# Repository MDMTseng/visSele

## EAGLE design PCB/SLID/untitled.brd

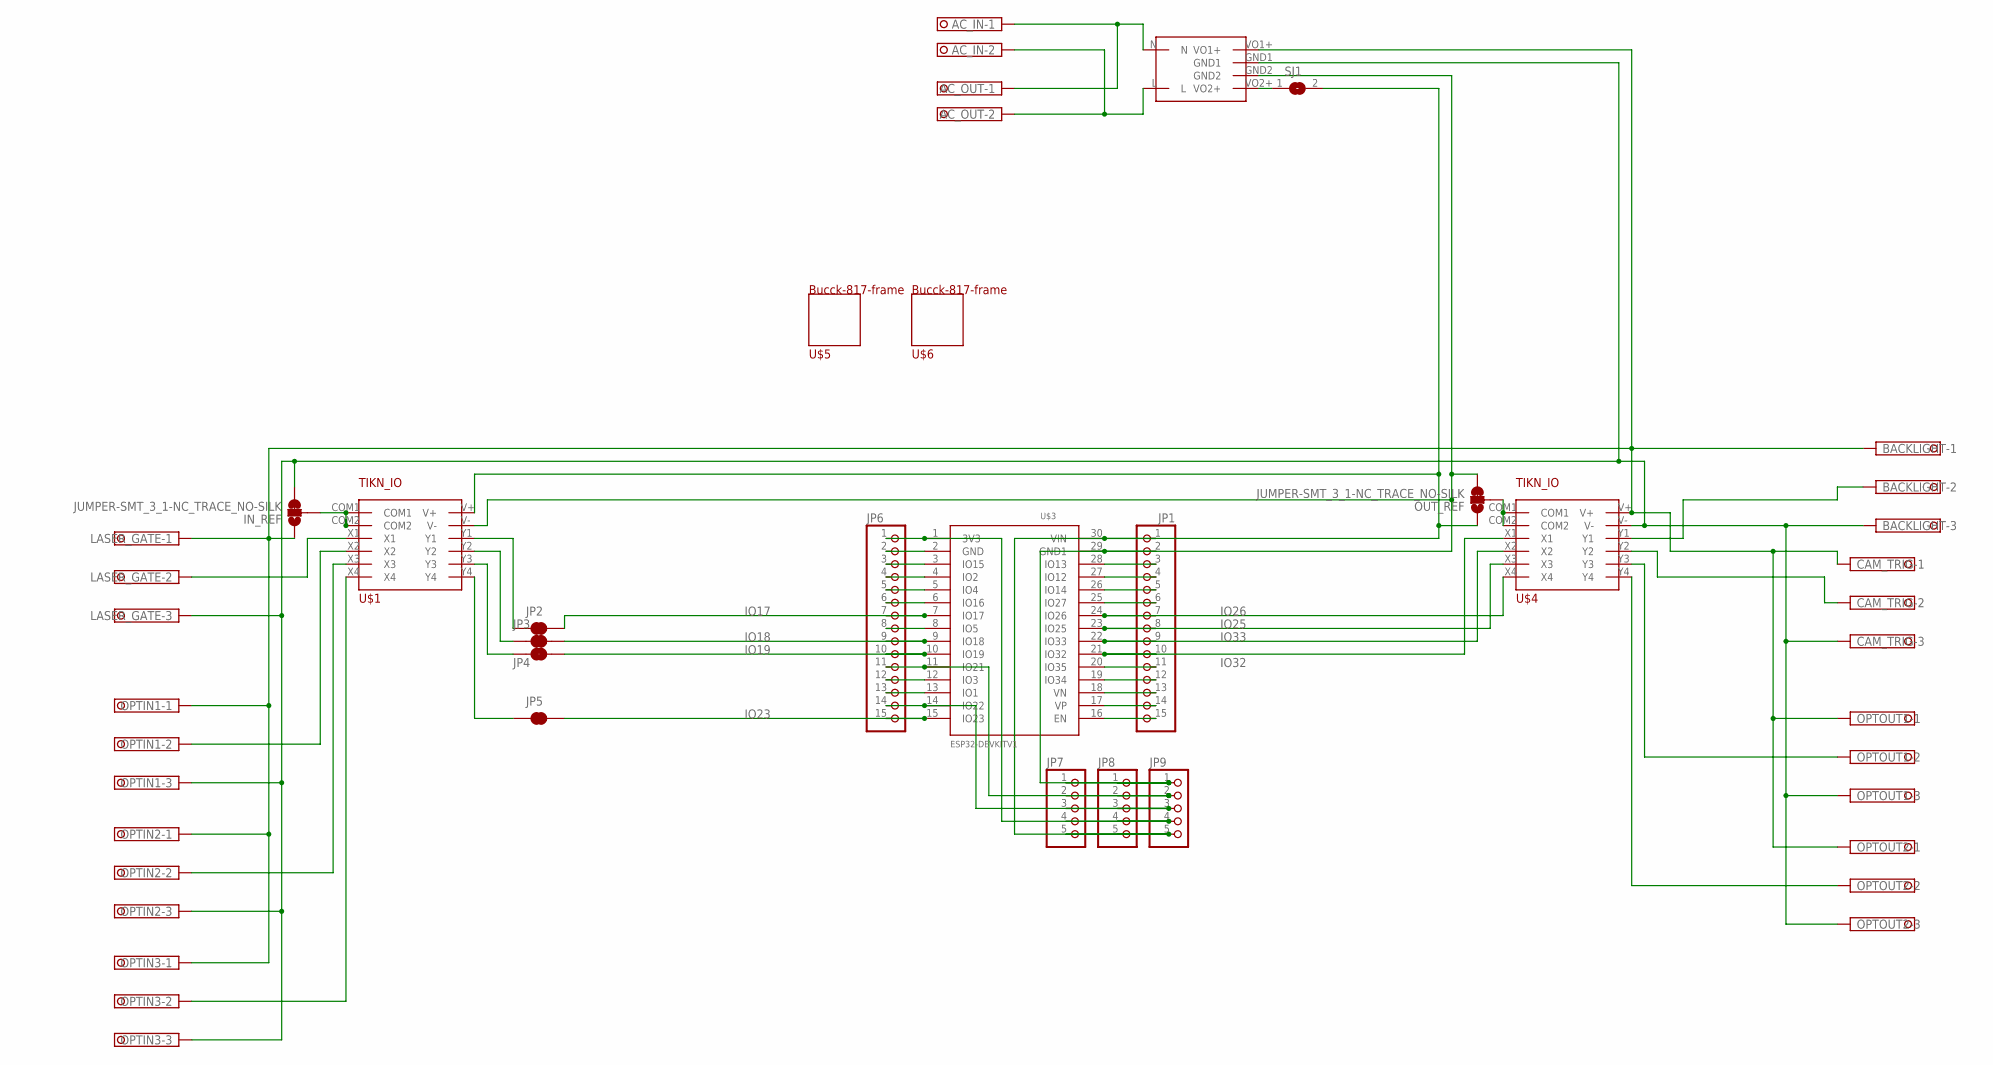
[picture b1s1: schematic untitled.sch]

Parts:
AC_IN: TERMINAL-BLOCK-3.5MM-2-PIN-LONG-PAD; TERMINAL-BLOCK-2-PIN-3.5MM-LONG-PAD
AC_OUT: TERMINAL-BLOCK-3.5MM-2-PIN-LONG-PAD; TERMINAL-BLOCK-2-PIN-3.5MM-LONG-PAD
BACKLIGHT: TERMINAL-BLOCK-3.5MM-3-PIN-LONG-PAD; TERMINAL-BLOCK-3-PIN-3.5MM-LONG-PAD
CAM_TRIG: TERMINAL-BLOCK-3.5MM-3-PIN-LONG-PAD; TERMINAL-BLOCK-3-PIN-3.5MM-LONG-PAD
IN_REF: JUMPER-SMT_3_1-NC_TRACE_NO-SILK; SMT-JUMPER_3_1-NC_TRACE_NO-SILK
JP1, JP6: PINHD-1X15; 1X15
JP2, JP3, JP4, JP5: JUMPER-SMT_2_NC_TRACE_SILK; SMT-JUMPER_2_NC_TRACE_SILK
JP7, JP8, JP9: PINHD-1X5; 1X05
LASER_GATE: TERMINAL-BLOCK-3.5MM-3-PIN-LONG-PAD; TERMINAL-BLOCK-3-PIN-3.5MM-LONG-PAD
OPTIN1, OPTIN2, OPTIN3: TERMINAL-BLOCK-3.5MM-3-PIN-LONG-PAD; TERMINAL-BLOCK-3-PIN-3.5MM-LONG-PAD
OPTOUT1, OPTOUT2: TERMINAL-BLOCK-3.5MM-3-PIN-LONG-PAD; TERMINAL-BLOCK-3-PIN-3.5MM-LONG-PAD
OUT_REF: JUMPER-SMT_3_1-NC_TRACE_NO-SILK; SMT-JUMPER_3_1-NC_TRACE_NO-SILK
SJ1: SJW
U$1, U$4: TIKN_IO_ISOLATOR2; IO_ISOLATOR2
U$2: AM22-24W1205V
U$3: ESP32DEVKITV1; ESP32-DEVKITV1
U$5, U$6: BUCC-817; BUCCK-817

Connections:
IO17: JP2.2, JP6.7, U$3.7 (IO17)
IO18: JP3.2, JP6.9, U$3.9 (IO18)
IO19: JP4.2, JP6.10, U$3.10 (IO19)
IO23: JP5.2, JP6.15, U$3.15 (IO23)
IO25: JP1.8, U$3.23 (IO25), U$4.X3
IO26: JP1.7, U$3.24 (IO26), U$4.X4
IO32: JP1.10, U$3.21 (IO32), U$4.X1
IO33: JP1.9, U$3.22 (IO33), U$4.X2
unnamed: JP1.1, JP7.5, JP8.5, JP9.5, OUT_REF.1, SJ1.2, U$1.V+, U$3.30 (VIN)
unnamed: SJ1.1, U$2.VO2+
unnamed: JP1.2, JP7.1, JP8.1, JP9.1, OUT_REF.3, U$1.V-, U$2.GND2, U$3.29 (GND1)
unnamed: BACKLIGHT.3, CAM_TRIG.3, IN_REF.3, LASER_GATE.3, OPTIN1.3, OPTIN2.3, OPTIN3.3, OPTOUT1.3, OPTOUT2.3, U$2.GND1, U$4.V-
unnamed: IN_REF.2, U$1.COM1, U$1.COM2
unnamed: OUT_REF.2, U$4.COM1, U$4.COM2
unnamed: JP2.1, U$1.Y1
unnamed: BACKLIGHT.1, CAM_TRIG.1, IN_REF.1, LASER_GATE.1, OPTIN1.1, OPTIN2.1, OPTIN3.1, OPTOUT1.1, OPTOUT2.1, U$2.VO1+, U$4.V+
unnamed: JP5.1, U$1.Y4
unnamed: JP4.1, U$1.Y3
unnamed: JP3.1, U$1.Y2
unnamed: JP6.8, U$3.8 (IO5)
unnamed: AC_IN.1, AC_OUT.1, U$2.N
unnamed: BACKLIGHT.2, U$4.Y1
unnamed: AC_IN.2, AC_OUT.2, U$2.L
unnamed: LASER_GATE.2, U$1.X1
unnamed: CAM_TRIG.2, U$4.Y2
unnamed: OPTIN1.2, U$1.X2
unnamed: OPTIN2.2, U$1.X3
unnamed: OPTIN3.2, U$1.X4
unnamed: OPTOUT1.2, U$4.Y3
unnamed: OPTOUT2.2, U$4.Y4
unnamed: JP6.1, JP7.4, JP8.4, JP9.4, U$3.1 (3V3)
unnamed: JP6.2, U$3.2 (GND)
unnamed: JP6.3, U$3.3 (IO15)
unnamed: JP6.4, U$3.4 (IO2)
unnamed: JP6.5, U$3.5 (IO4)
unnamed: JP6.6, U$3.6 (IO16)
unnamed: JP6.11, JP7.2, JP8.2, JP9.2, U$3.11 (IO21)
unnamed: JP6.12, U$3.12 (IO3)
unnamed: JP6.13, U$3.13 (IO1)
unnamed: JP6.14, JP7.3, JP8.3, JP9.3, U$3.14 (IO22)
unnamed: JP1.3, U$3.28 (IO13)
unnamed: JP1.4, U$3.27 (IO12)
unnamed: JP1.5, U$3.26 (IO14)
unnamed: JP1.6, U$3.25 (IO27)
unnamed: JP1.11, U$3.20 (IO35)
unnamed: JP1.12, U$3.19 (IO34)
unnamed: JP1.13, U$3.18 (VN)
unnamed: JP1.14, U$3.17 (VP)
unnamed: JP1.15, U$3.16 (EN)

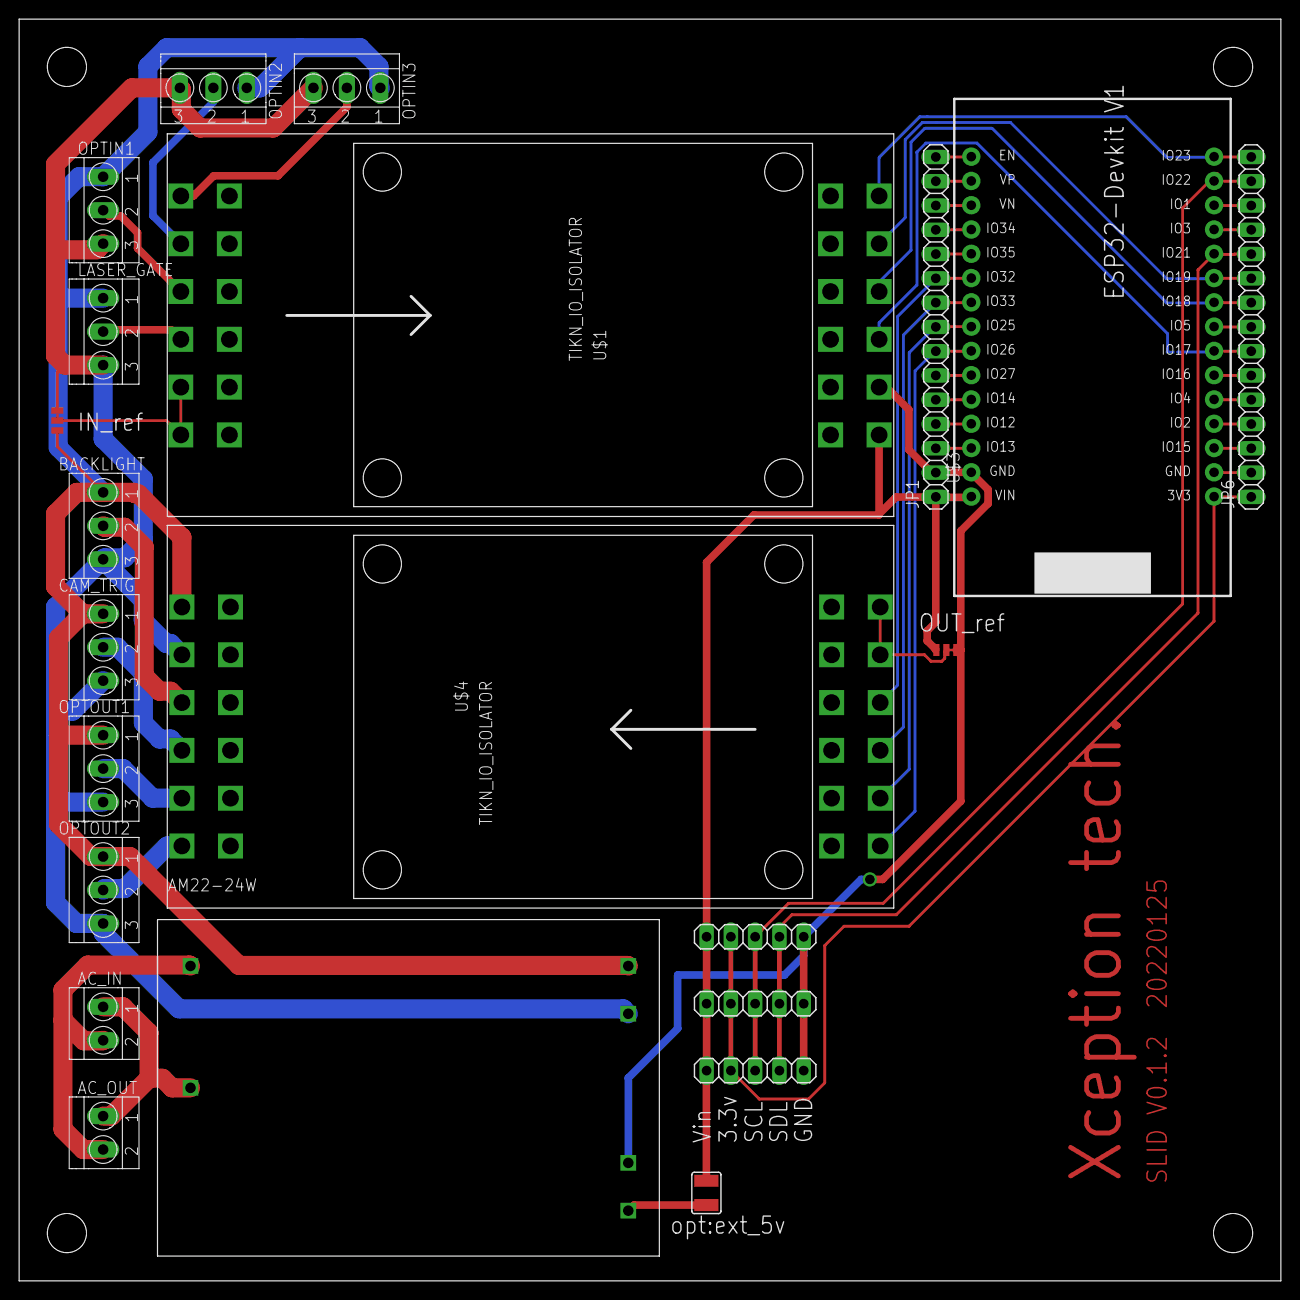
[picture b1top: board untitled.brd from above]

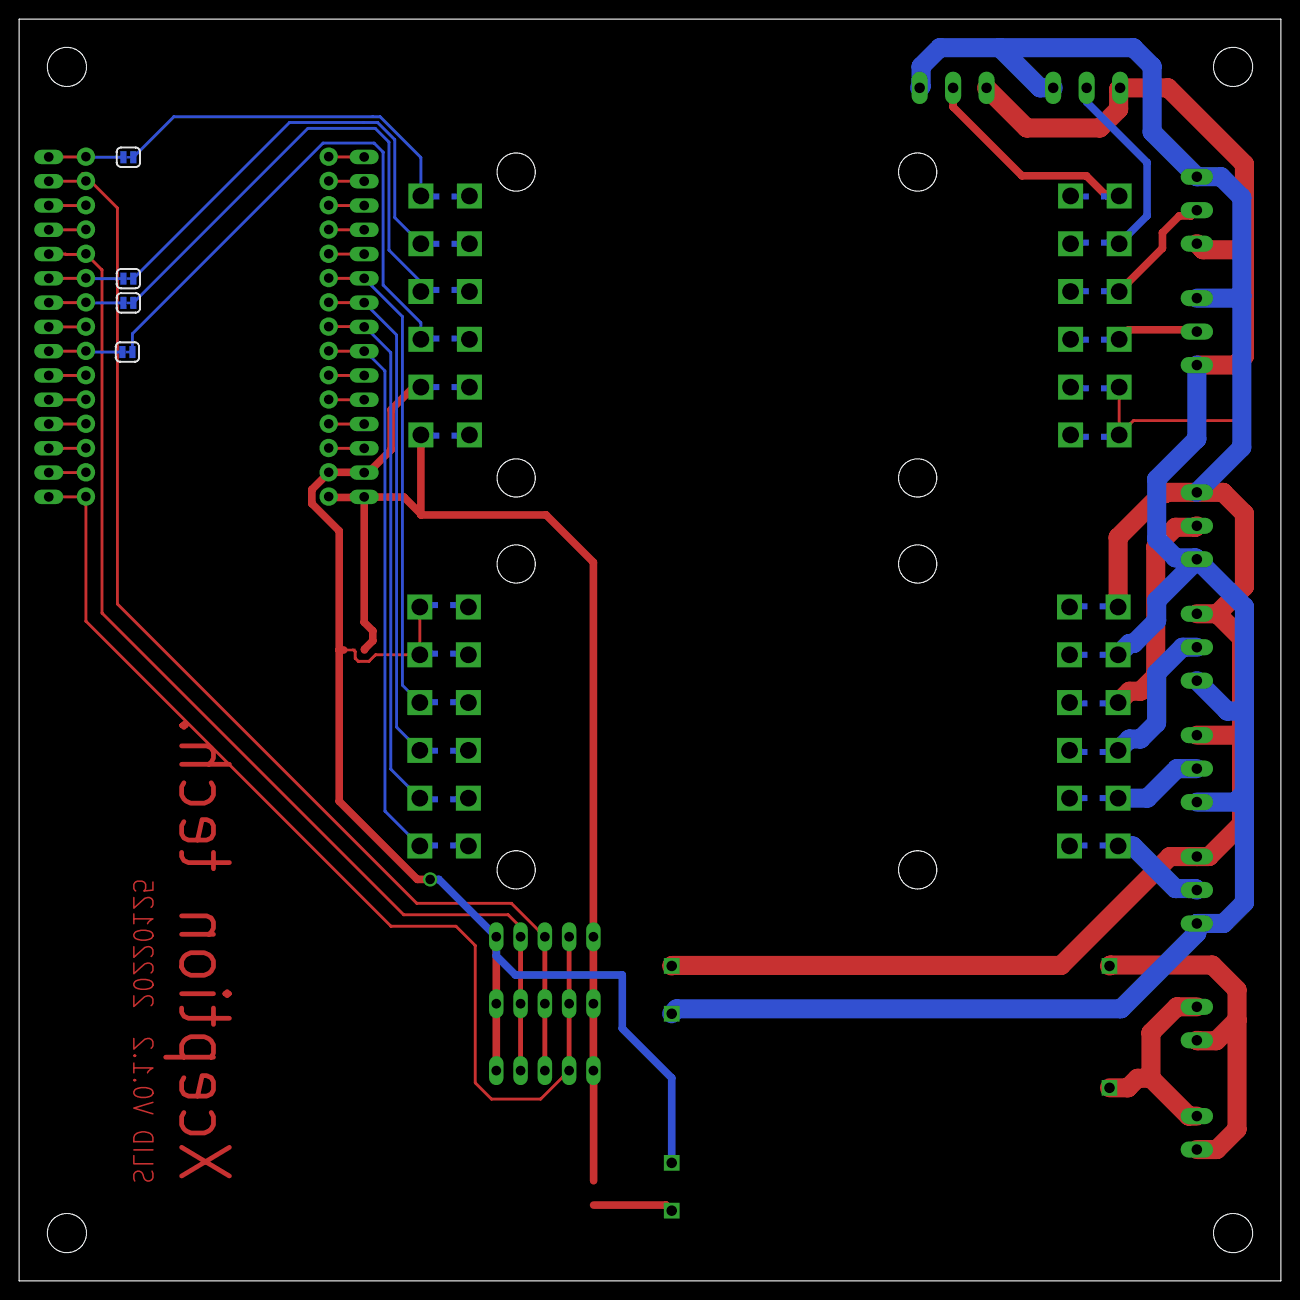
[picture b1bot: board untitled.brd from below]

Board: 2 copper layers, 132.0 x 132.0 mm, 28 parts (4 on the bottom side), 49 nets.

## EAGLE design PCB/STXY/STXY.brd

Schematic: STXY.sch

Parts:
C2: C2.5/2; C2.5-2
EIO1_A6, EIO1_A7, EIO1_A8: JUMPER-SMT_3_1-NC_TRACE_SILK; SMT-JUMPER_3_1-NC_TRACE_SILK
ETH0: WIZ820IO_DEVICE'DUAL-IN-LINE'; WIZ820IO
EXIO1, EXIO2: PCF8574T; SO16W
INT_JUMP1: JUMPER-SMT_3_1-NC_TRACE_SILK; SMT-JUMPER_3_1-NC_TRACE_SILK
J1, J2: F-1X20-SIP-100-32; SIP-100-20-32
J8, J10, J11, J12, J13, J14, J15, J17: F-2X12-DIL-100_M; DIL-100-2X12_M
JP1, JP2, JP3: JUMPER-SMT_3_1-NC_TRACE_SILK; SMT-JUMPER_3_1-NC_TRACE_SILK
J_SK9822: F-1X04-SIP-100-40Y; SIP-100-04-40Y
MOT1_!EN1, MOT1_!FLT1, MOT1_!RST1, MOT1_!SLP1, MOT1_M3, MOT1_M4, MOT1_M5, MOT1_MCU_GND1, MOT1_MCU_VDD1, MOT1_MD_DIR1, MOT1_MD_STEP1, MOT1_MOT_GND1, MOT1_MOT_VMOT1, MOT1_SENSOR_SFAR1, MOT1_SENSOR_SMID1, MOT1_SENSOR_SNEAR1, MOT1_SENSOR_VDD1, MOT2_!EN1, MOT2_!FLT1, MOT2_!RST1, MOT2_!SLP1, MOT2_M3, MOT2_M4, MOT2_M5, MOT2_MCU_GND1, MOT2_MCU_VDD1, MOT2_MD_DIR1, MOT2_MD_STEP1, MOT2_MOT_GND1, MOT2_MOT_VMOT1, MOT2_SENSOR_SFAR1, MOT2_SENSOR_SMID1, MOT2_SENSOR_SNEAR1, MOT2_SENSOR_VDD1, MOT3_!EN1, MOT3_!FLT1, MOT3_!RST1, MOT3_!SLP1, MOT3_M3, MOT3_M4, MOT3_M5, MOT3_MCU_GND1, MOT3_MCU_VDD1, MOT3_MD_DIR1, MOT3_MD_STEP1, MOT3_MOT_GND1, MOT3_MOT_VMOT1, MOT3_SENSOR_SFAR1, MOT3_SENSOR_SMID1, MOT3_SENSOR_SNEAR1, MOT3_SENSOR_VDD1: SHORTT5; SHORT_TOP-50
MOT1_CON1, MOT2_CON1, MOT3_CON1: F09VP
MOT1_DRV1, MOT2_DRV1, MOT3_DRV1: 2133-DRV8825; DRV8825
MOT1_DRV_OPT3, MOT2_DRV_OPT3, MOT3_DRV_OPT3: TERMINAL-BLOCK-3.5MM-9-PIN-ROUND-PAD; TERMINAL-BLOCK-9-PIN-3.5MM-ROUND-PAD
MOT1_DRV_OPT4, MOT2_DRV_OPT4, MOT3_DRV_OPT4: JST-XH-09-PIN-LONG-PAD; JST-XH-09-PACKAGE-LONG-PAD
POW_EUROSTYLE: TERMINAL-BLOCK-3.5MM-4-PIN-LONG-PAD; TERMINAL-BLOCK-4-PIN-3.5MM-LONG-PAD
R7, R8, R9, R10, R11, R12, R13, R14, R15, R16, R17, R18, R25, R26, R27, R28, R29, R30: 10KOHM-0603-1/10W-1%; 0603
U1: ESP32DEVKITC; ESP32-DEVKITC
X1: EMG_BTN; JST-XH-03-PACKAGE-LONG-PAD
X2: TERMINAL-BLOCK-3.5MM-3-PIN-LONG-PAD; TERMINAL-BLOCK-3-PIN-3.5MM-LONG-PAD
X3, X4, X5, X6, X7: JST-XH-12-PIN-LONG-PAD; JST-XH-12-PACKAGE-LONG-PAD

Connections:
EMG_SIG: J1.15, U1.15 (IO13), X1.3, X2.3
ETH0_INT: ETH0.J1.6 (/INT), EXIO2.12 (P7), X3.12, X4.12
EXIO1_INT: EXIO1.13 (!INT), J2.13, U1.31 (IO19)
EXT_5V: EXIO1.1 (A0), EXIO1.16 (VDD), EXIO2.2 (A1), EXIO2.16 (VDD), J1.19, JP1.3, JP2.1, JP3.3, J_SK9822.1, MOT1_MCU_VDD1.1, MOT1_SENSOR_VDD1.1, MOT2_MCU_VDD1.1, MOT2_SENSOR_VDD1.1, MOT3_MCU_VDD1.1, MOT3_SENSOR_VDD1.1, POW_EUROSTYLE.3, U1.19 (5V), X1.2, X2.2, X3.3, X4.3, X5.3, X6.3, X7.3; also elsewhere on the board
EXT_24V: MOT1_MOT_VMOT1.1, MOT2_MOT_VMOT1.1, MOT3_MOT_VMOT1.1, POW_EUROSTYLE.1, X3.1, X4.1, X5.1, X6.1, X7.1
EXT_24V_GND: MOT1_MOT_GND1.1, MOT2_MOT_GND1.1, MOT3_MOT_GND1.1, POW_EUROSTYLE.2, X3.2, X4.2, X5.2, X6.2, X7.2
EXT_GND: ETH0.J1.1 (GND1), ETH0.J1.2 (GND2), ETH0.J2.1 (GND3), EXIO1.2 (A1), EXIO1.3 (A2), EXIO1.8 (VSS), EXIO2.1 (A0), EXIO2.3 (A2), EXIO2.8 (VSS), INT_JUMP1.1, J1.14, J2.14, J2.20, JP1.1, JP2.3, JP3.1, J_SK9822.4, MOT1_!RST1.1, MOT1_!SLP1.1, MOT1_MCU_GND1.1, MOT2_!RST1.1, MOT2_!SLP1.1, MOT2_MCU_GND1.1, MOT3_!RST1.1, MOT3_!SLP1.1, MOT3_MCU_GND1.1, POW_EUROSTYLE.4, U1.14 (GND), U1.32 (GND), U1.38 (GND), X1.1, X2.1, X3.4, X4.4, X5.4, X6.4, X7.4; also elsewhere on the board
LED_ARR_CLK: J2.9, J_SK9822.2, U1.27 (IO16)
MOT1_!EN: MOT1_!EN1.2, MOT1_DRV1.1 (!EN), MOT1_DRV_OPT3.7, MOT1_DRV_OPT4.7
MOT1_!FLT: MOT1_!FLT1.2, MOT1_DRV1.10 (!FLT)
MOT1_!RST: MOT1_!RST1.2, MOT1_DRV1.5 (!RST)
MOT1_!SLP: MOT1_!SLP1.2, MOT1_DRV1.6 (!SLP)
MOT1_M0: MOT1_DRV1.2 (M0), MOT1_M3.2
MOT1_M1: MOT1_DRV1.3 (M1), MOT1_M4.2
MOT1_M2: MOT1_DRV1.4 (M2), MOT1_M5.2
MOT1_MCU_GND: MOT1_CON1.2, MOT1_DRV1.9 (GND1), MOT1_MCU_GND1.2, R8.1, R10.1, R12.1
MOT1_MCU_VDD: MOT1_MCU_VDD1.2, R7.2, R9.2, R11.2
MOT1_MD_DIR: MOT1_DRV1.8 (DIR), MOT1_DRV_OPT3.9, MOT1_DRV_OPT4.9, MOT1_MD_DIR1.2
MOT1_MD_STEP: MOT1_DRV1.7 (STEP), MOT1_DRV_OPT3.8, MOT1_DRV_OPT4.8, MOT1_MD_STEP1.2
MOT1_MOT_GND: MOT1_DRV1.15 (GND2), MOT1_DRV_OPT3.5, MOT1_DRV_OPT4.5, MOT1_MOT_GND1.2
MOT1_MOT_VMOT: MOT1_DRV1.16 (VMOT), MOT1_DRV_OPT3.6, MOT1_DRV_OPT4.6, MOT1_MOT_VMOT1.2
MOT1_SENSOR_SFAR: MOT1_CON1.5, MOT1_SENSOR_SFAR1.2, R11.1, R12.2
MOT1_SENSOR_SMID: MOT1_CON1.4, MOT1_SENSOR_SMID1.2, R9.1, R10.2
MOT1_SENSOR_SNEAR: MOT1_CON1.3, MOT1_SENSOR_SNEAR1.2, R7.1, R8.2
MOT1_SENSOR_VDD: MOT1_CON1.1, MOT1_SENSOR_VDD1.2
MOT1_SOCK_A+: MOT1_CON1.6, MOT1_DRV1.12 (A1), MOT1_DRV_OPT3.1, MOT1_DRV_OPT4.1
MOT1_SOCK_A-: MOT1_CON1.7, MOT1_DRV1.11 (A2), MOT1_DRV_OPT3.2, MOT1_DRV_OPT4.2
MOT1_SOCK_B+: MOT1_CON1.8, MOT1_DRV1.13 (B1), MOT1_DRV_OPT3.3, MOT1_DRV_OPT4.3
MOT1_SOCK_B-: MOT1_CON1.9, MOT1_DRV1.14 (B2), MOT1_DRV_OPT3.4, MOT1_DRV_OPT4.4
MOT2_!EN: MOT2_!EN1.2, MOT2_DRV1.1 (!EN), MOT2_DRV_OPT3.7, MOT2_DRV_OPT4.7
MOT2_!FLT: MOT2_!FLT1.2, MOT2_DRV1.10 (!FLT)
MOT2_!RST: MOT2_!RST1.2, MOT2_DRV1.5 (!RST)
MOT2_!SLP: MOT2_!SLP1.2, MOT2_DRV1.6 (!SLP)
MOT2_M0: MOT2_DRV1.2 (M0), MOT2_M3.2
MOT2_M1: MOT2_DRV1.3 (M1), MOT2_M4.2
MOT2_M2: MOT2_DRV1.4 (M2), MOT2_M5.2
MOT2_MCU_GND: MOT2_CON1.2, MOT2_DRV1.9 (GND1), MOT2_MCU_GND1.2, R14.1, R16.1, R18.1
MOT2_MCU_VDD: MOT2_MCU_VDD1.2, R13.2, R15.2, R17.2
MOT2_MD_DIR: MOT2_DRV1.8 (DIR), MOT2_DRV_OPT3.9, MOT2_DRV_OPT4.9, MOT2_MD_DIR1.2
MOT2_MD_STEP: MOT2_DRV1.7 (STEP), MOT2_DRV_OPT3.8, MOT2_DRV_OPT4.8, MOT2_MD_STEP1.2
MOT2_MOT_GND: MOT2_DRV1.15 (GND2), MOT2_DRV_OPT3.5, MOT2_DRV_OPT4.5, MOT2_MOT_GND1.2
MOT2_MOT_VMOT: MOT2_DRV1.16 (VMOT), MOT2_DRV_OPT3.6, MOT2_DRV_OPT4.6, MOT2_MOT_VMOT1.2
MOT2_SENSOR_SFAR: MOT2_CON1.5, MOT2_SENSOR_SFAR1.2, R17.1, R18.2
MOT2_SENSOR_SMID: MOT2_CON1.4, MOT2_SENSOR_SMID1.2, R15.1, R16.2
MOT2_SENSOR_SNEAR: MOT2_CON1.3, MOT2_SENSOR_SNEAR1.2, R13.1, R14.2
MOT2_SENSOR_VDD: MOT2_CON1.1, MOT2_SENSOR_VDD1.2
MOT2_SOCK_A+: MOT2_CON1.6, MOT2_DRV1.12 (A1), MOT2_DRV_OPT3.1, MOT2_DRV_OPT4.1
MOT2_SOCK_A-: MOT2_CON1.7, MOT2_DRV1.11 (A2), MOT2_DRV_OPT3.2, MOT2_DRV_OPT4.2
MOT2_SOCK_B+: MOT2_CON1.8, MOT2_DRV1.13 (B1), MOT2_DRV_OPT3.3, MOT2_DRV_OPT4.3
MOT2_SOCK_B-: MOT2_CON1.9, MOT2_DRV1.14 (B2), MOT2_DRV_OPT3.4, MOT2_DRV_OPT4.4
MOT3_!EN: MOT3_!EN1.2, MOT3_DRV1.1 (!EN), MOT3_DRV_OPT3.7, MOT3_DRV_OPT4.7
MOT3_!FLT: MOT3_!FLT1.2, MOT3_DRV1.10 (!FLT)
MOT3_!RST: MOT3_!RST1.2, MOT3_DRV1.5 (!RST)
MOT3_!SLP: MOT3_!SLP1.2, MOT3_DRV1.6 (!SLP)
MOT3_M0: MOT3_DRV1.2 (M0), MOT3_M3.2
MOT3_M1: MOT3_DRV1.3 (M1), MOT3_M4.2
MOT3_M2: MOT3_DRV1.4 (M2), MOT3_M5.2
MOT3_MCU_GND: MOT3_CON1.2, MOT3_DRV1.9 (GND1), MOT3_MCU_GND1.2, R26.1, R28.1, R30.1
MOT3_MCU_VDD: MOT3_MCU_VDD1.2, R25.2, R27.2, R29.2
MOT3_MD_DIR: MOT3_DRV1.8 (DIR), MOT3_DRV_OPT3.9, MOT3_DRV_OPT4.9, MOT3_MD_DIR1.2
MOT3_MD_STEP: MOT3_DRV1.7 (STEP), MOT3_DRV_OPT3.8, MOT3_DRV_OPT4.8, MOT3_MD_STEP1.2
MOT3_MOT_GND: MOT3_DRV1.15 (GND2), MOT3_DRV_OPT3.5, MOT3_DRV_OPT4.5, MOT3_MOT_GND1.2
MOT3_MOT_VMOT: MOT3_DRV1.16 (VMOT), MOT3_DRV_OPT3.6, MOT3_DRV_OPT4.6, MOT3_MOT_VMOT1.2
MOT3_SENSOR_SFAR: MOT3_CON1.5, MOT3_SENSOR_SFAR1.2, R29.1, R30.2
MOT3_SENSOR_SMID: MOT3_CON1.4, MOT3_SENSOR_SMID1.2, R27.1, R28.2
MOT3_SENSOR_SNEAR: MOT3_CON1.3, MOT3_SENSOR_SNEAR1.2, R25.1, R26.2
MOT3_SENSOR_VDD: MOT3_CON1.1, MOT3_SENSOR_VDD1.2
MOT3_SOCK_A+: MOT3_CON1.6, MOT3_DRV1.12 (A1), MOT3_DRV_OPT3.1, MOT3_DRV_OPT4.1
MOT3_SOCK_A-: MOT3_CON1.7, MOT3_DRV1.11 (A2), MOT3_DRV_OPT3.2, MOT3_DRV_OPT4.2
MOT3_SOCK_B+: MOT3_CON1.8, MOT3_DRV1.13 (B1), MOT3_DRV_OPT3.3, MOT3_DRV_OPT4.3
MOT3_SOCK_B-: MOT3_CON1.9, MOT3_DRV1.14 (B2), MOT3_DRV_OPT3.4, MOT3_DRV_OPT4.4
MOTXY_M0: JP1.2, MOT1_M3.1, MOT2_M3.1, MOT3_M3.1
MOTXY_M1: JP2.2, MOT1_M4.1, MOT2_M4.1, MOT3_M4.1
MOTXY_M2: JP3.2, MOT1_M5.1, MOT2_M5.1, MOT3_M5.1
MOTX_DIR: J1.12, MOT1_MD_DIR1.1, U1.12 (IO14)
MOTX_SENSOR_FAR: EXIO1.4 (P0), MOT1_SENSOR_SFAR1.1, X5.5, X6.5
MOTX_SENSOR_NEAR: EIO1_A6.2, MOT1_SENSOR_SNEAR1.1
MOTX_STEP: J1.11, MOT1_MD_STEP1.1, U1.11 (IO27)
MOTY_DIR: J1.10, MOT2_MD_DIR1.1, U1.10 (IO26)
MOTY_SENSOR_FAR: EXIO1.5 (P1), MOT2_SENSOR_SFAR1.1, X5.6, X6.6
MOTY_SENSOR_NEAR: EIO1_A7.2, MOT2_SENSOR_SNEAR1.1
MOTY_STEP: J1.9, MOT2_MD_STEP1.1, U1.9 (IO25)
MOTZ_DIR: J1.8, MOT3_MD_DIR1.1, U1.8 (IO33)
MOTZ_SENSOR_FAR: EXIO1.6 (P2), MOT3_SENSOR_SFAR1.1, X5.7, X6.7
MOTZ_SENSOR_NEAR: EIO1_A8.2, MOT3_SENSOR_SNEAR1.1
MOTZ_STEP: J1.7, MOT3_MD_STEP1.1, U1.7 (IO32)
MOT_EN: J1.13, MOT1_!EN1.1, MOT2_!EN1.1, MOT3_!EN1.1, U1.13 (IO12)
unnamed: EXIO1.12 (P7), X5.12, X6.12
unnamed: EXIO1.11 (P6), X5.11, X6.11
unnamed: EXIO2.4 (P0), X3.5, X4.5
unnamed: EXIO2.5 (P1), X3.6, X4.6
unnamed: EXIO2.6 (P2), X3.7, X4.7
unnamed: EXIO2.7 (P3), X3.8, X4.8
unnamed: EXIO2.9 (P4), X3.9, X4.9
unnamed: J1.18, U1.18 (CMD)
unnamed: EXIO2.10 (P5), X3.10, X4.10
unnamed: ETH0.J1.5 (/SS), INT_JUMP1.2
unnamed: EXIO2.11 (P6), X3.11, X4.11
OENCX_A+: J1.3, U1.3 (SVP); also elsewhere on the board
OENCX_B+: J1.4, U1.4 (SVN); also elsewhere on the board
OENCY_A+: J1.5, U1.5 (IO34); also elsewhere on the board
OENCY_B+: J1.6, U1.6 (IO35); also elsewhere on the board
OPT0/ETH0_SEL: INT_JUMP1.3, J2.6, U1.24 (IO2), X7.5
OPT1/U1_MISO: ETH0.J2.6 (MISO), J2.7, U1.25 (IO0), X7.6
OPT2/EXIO2_INT: EXIO2.13 (!INT), J2.8, U1.26 (IO4), X7.7
OPT3/U1_SCLK: ETH0.J1.4 (SCLK), J2.10, U1.28 (IO17), X7.8
OPT_MOTX_SENSOR_NEAR: EIO1_A6.1, EXIO1.7 (P3), X5.8, X6.8
OPT_MOTY_SENSOR_NEAR: EIO1_A7.1, EXIO1.9 (P4), X5.9, X6.9
OPT_MOTZ_SENSOR_NEAR: EIO1_A8.1, EXIO1.10 (P5), X5.10, X6.10
U1_3V3: C2.2, ETH0.J2.2 (VIN1), ETH0.J2.3 (VIN2), J1.1, U1.1 (3V3)
U1_CLK: J2.2, U1.20 (CLK)
U1_EN: C2.1, ETH0.J2.5 (/RESET), J1.2, U1.2 (EN)
U1_IO21: EIO1_A6.3, J2.15, U1.33 (IO21), X7.9
U1_IO22: EIO1_A7.3, J2.18, U1.36 (IO22), X7.10
U1_IO23: EIO1_A8.3, J2.19, U1.37 (IO23), X7.11
U1_MOSI: ETH0.J1.3 (MOSI), J2.5, J_SK9822.3, U1.23 (IO15)
U1_RXD0: J2.16, U1.34 (RXD0)
U1_SCL: EXIO1.14 (SCL), EXIO2.14 (SCL), J2.12, U1.30 (IO18)
U1_SD0: J2.3, U1.21 (SD0)
U1_SD1: J2.4, U1.22 (SD1)
U1_SD2: J1.16, U1.16 (SD2)
U1_SD3: J1.17, U1.17 (SD3)
U1_SDA: EXIO1.15 (SDA), EXIO2.15 (SDA), J2.11, U1.29 (IO5)
U1_TXD0: J2.17, U1.35 (TXD0)

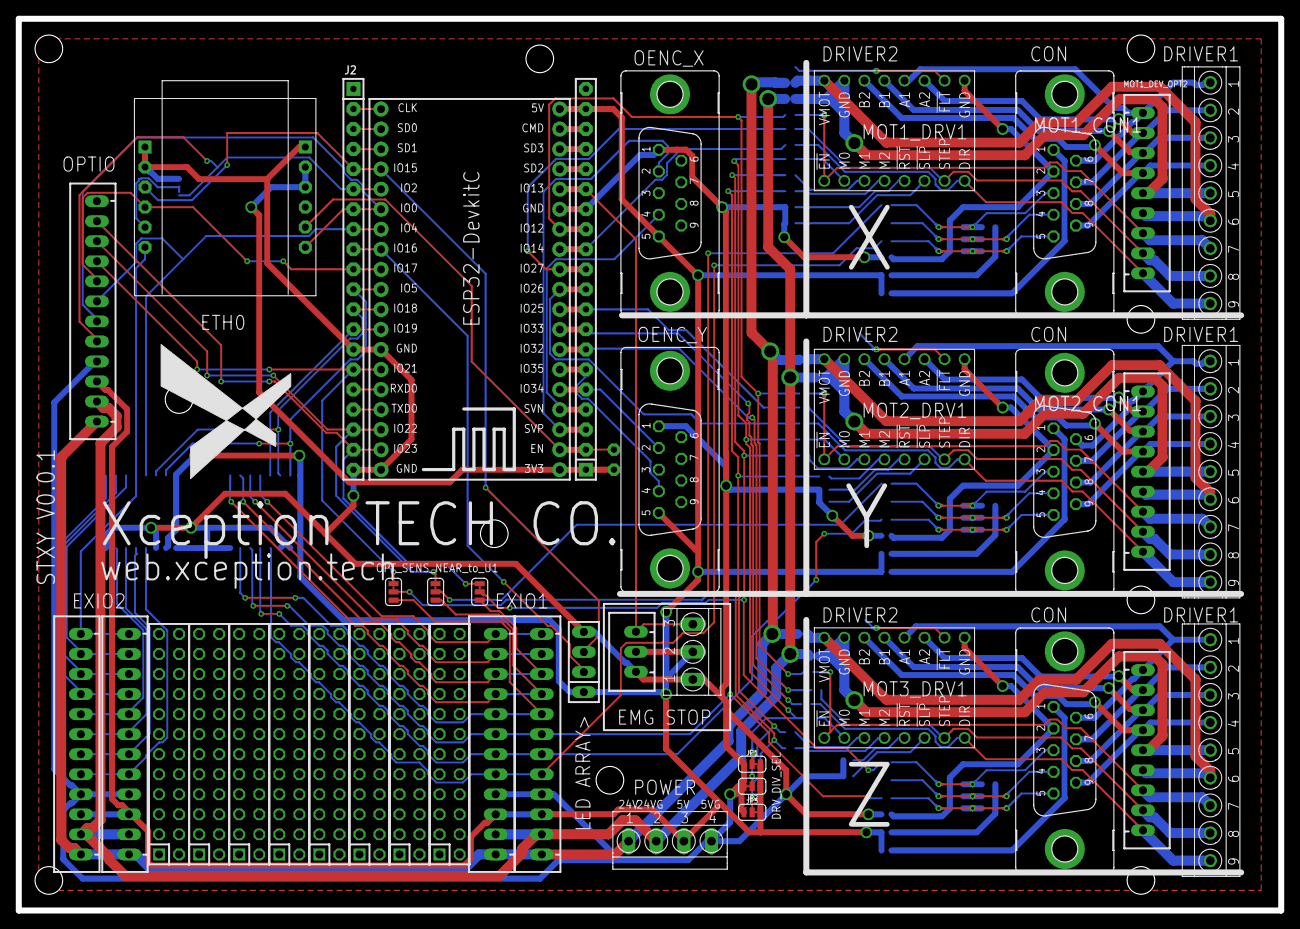
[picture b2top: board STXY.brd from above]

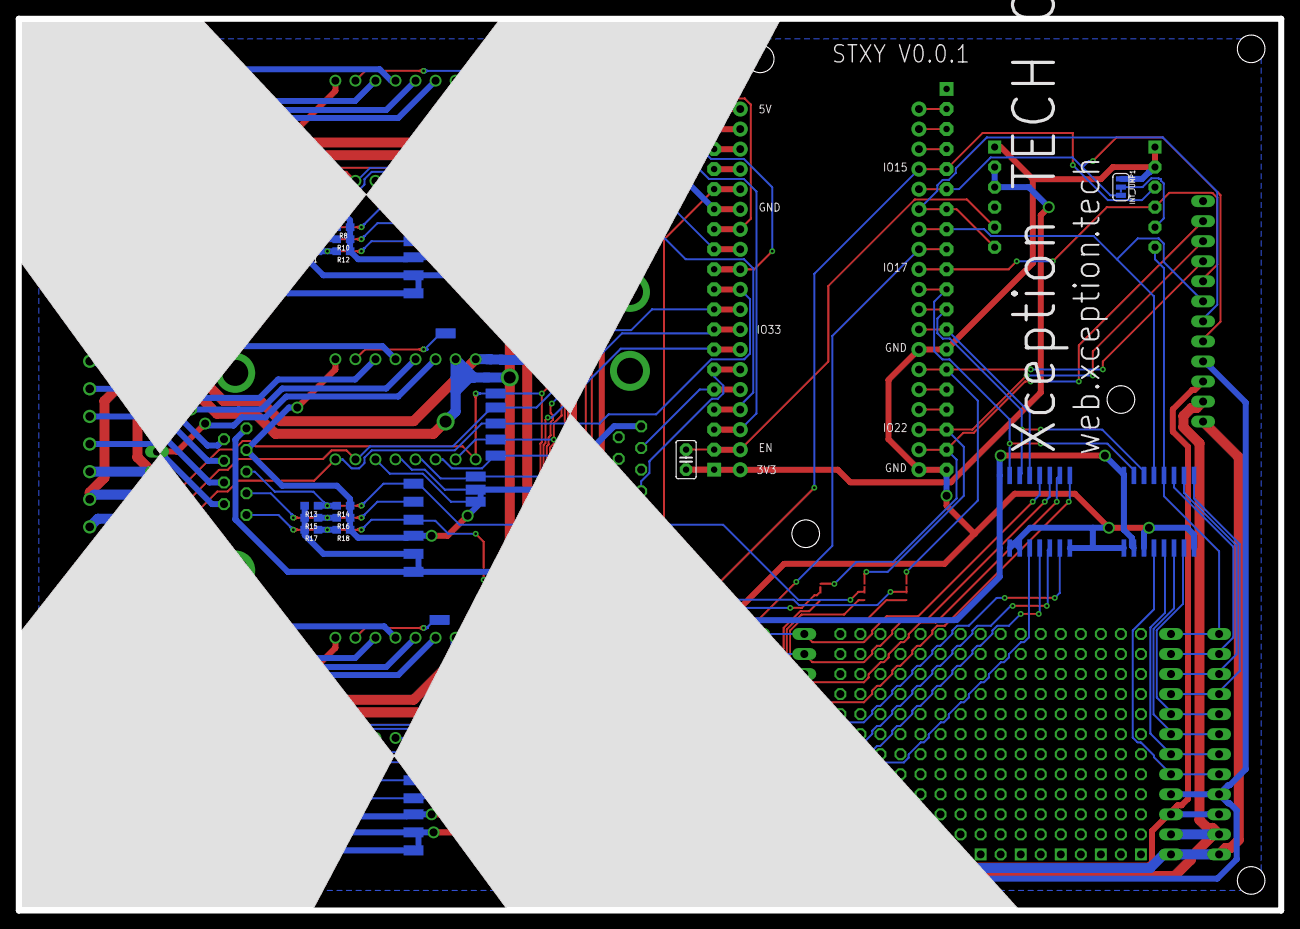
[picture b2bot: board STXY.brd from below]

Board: 2 copper layers, 160.0 x 113.0 mm, 114 parts (73 on the bottom side), 124 nets.

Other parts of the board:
OPTICAL_ENC_X:OENC: F09VP
OPTICAL_ENC_Y:OENC: F09VP

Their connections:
EXT_5V: OPTICAL_ENC_X:OENC.5, OPTICAL_ENC_Y:OENC.5; also elsewhere on the board
EXT_GND: OPTICAL_ENC_X:OENC.1, OPTICAL_ENC_Y:OENC.1; also elsewhere on the board
OENCX_A+: OPTICAL_ENC_X:OENC.2; also elsewhere on the board
OENCX_B+: OPTICAL_ENC_X:OENC.4; also elsewhere on the board
OENCY_A+: OPTICAL_ENC_Y:OENC.2; also elsewhere on the board
OENCY_B+: OPTICAL_ENC_Y:OENC.4; also elsewhere on the board

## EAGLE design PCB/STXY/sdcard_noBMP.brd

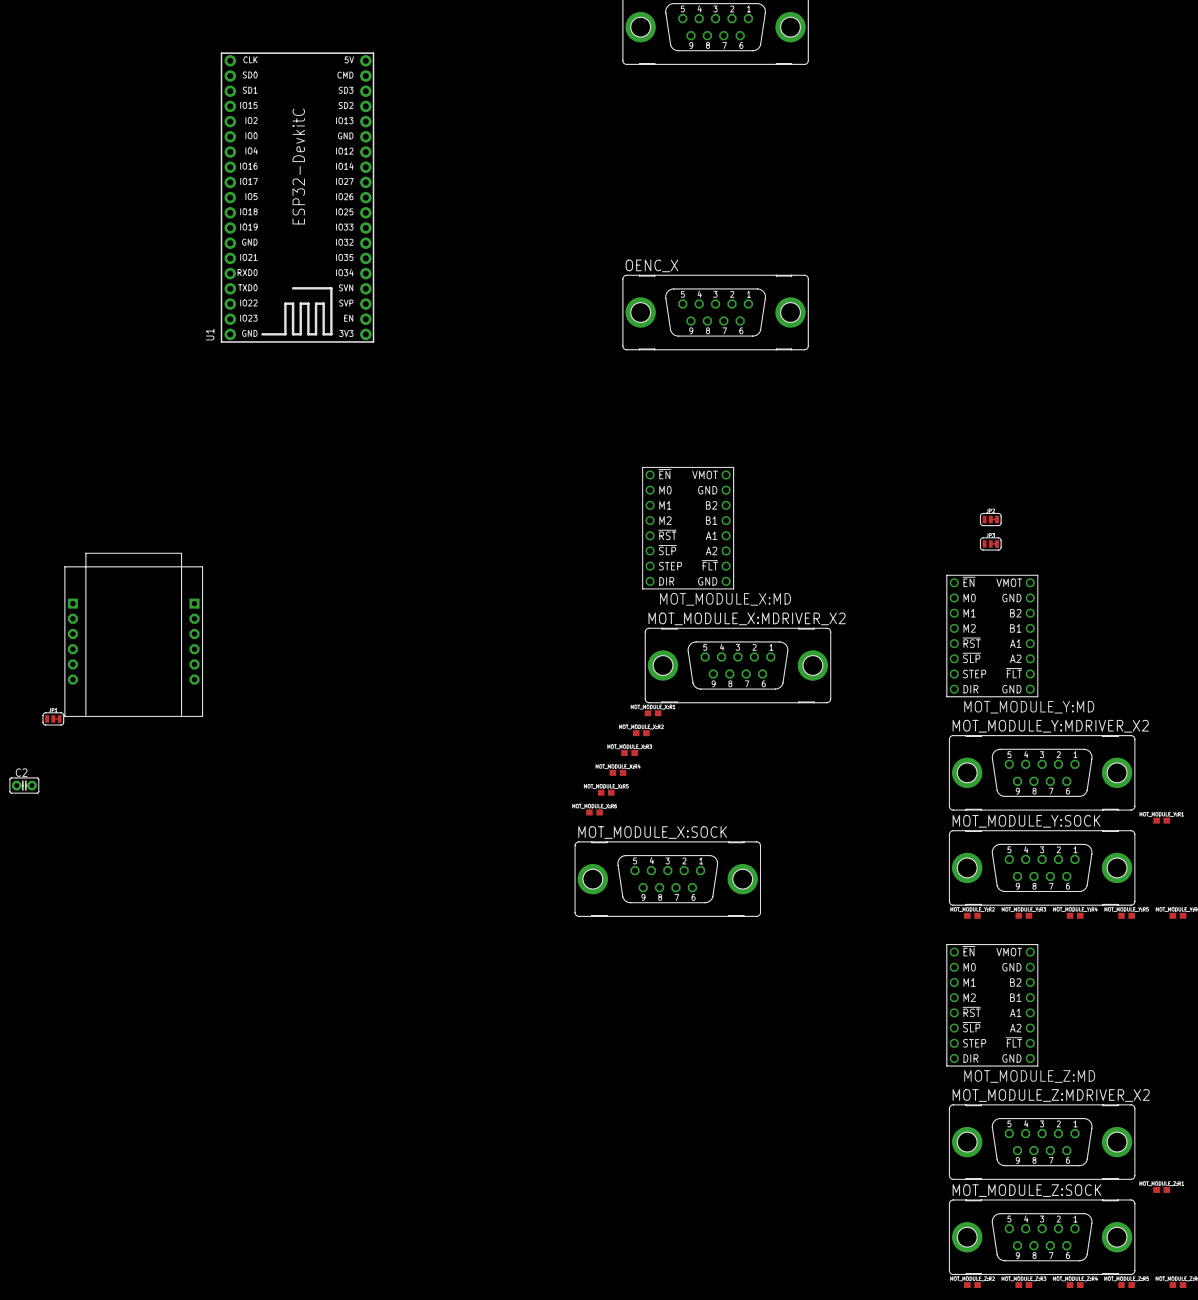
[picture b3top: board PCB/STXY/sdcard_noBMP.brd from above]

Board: 2 copper layers, 35 parts (0 on the bottom side), 39 nets, no tracks yet.

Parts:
C2: C2.5-2
ETH0: WIZ820IO
JP1, JP2, JP3: JUMPER-SMT_3_1-NC_TRACE_SILK; SMT-JUMPER_3_1-NC_TRACE_SILK
MOT_MODULE_X:MD: 2133-DRV8825; DRV8825
MOT_MODULE_X:MDRIVER_X2: F09VP
MOT_MODULE_X:R1, MOT_MODULE_X:R2, MOT_MODULE_X:R3, MOT_MODULE_X:R4, MOT_MODULE_X:R5, MOT_MODULE_X:R6: 10k; 0603
MOT_MODULE_X:SOCK: F09VP
MOT_MODULE_Y:MD: 2133-DRV8825; DRV8825
MOT_MODULE_Y:MDRIVER_X2: F09VP
MOT_MODULE_Y:R1, MOT_MODULE_Y:R2, MOT_MODULE_Y:R3, MOT_MODULE_Y:R4, MOT_MODULE_Y:R5, MOT_MODULE_Y:R6: 10k; 0603
MOT_MODULE_Y:SOCK: F09VP
MOT_MODULE_Z:MD: 2133-DRV8825; DRV8825
MOT_MODULE_Z:MDRIVER_X2: F09VP
MOT_MODULE_Z:R1, MOT_MODULE_Z:R2, MOT_MODULE_Z:R3, MOT_MODULE_Z:R4, MOT_MODULE_Z:R5, MOT_MODULE_Z:R6: 10k; 0603
MOT_MODULE_Z:SOCK: F09VP
OENC_X: F09VP
OENC_Y: F09VP
U1: ESP32DEVKITC; ESP32-DEVKITC

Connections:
EXT_5V: JP1.3, JP2.1, JP3.3, MOT_MODULE_X:MD.5, MOT_MODULE_X:MD.6, MOT_MODULE_X:R1.2, MOT_MODULE_X:R3.2, MOT_MODULE_X:R5.2, MOT_MODULE_X:SOCK.1, MOT_MODULE_Y:MD.5, MOT_MODULE_Y:MD.6, MOT_MODULE_Y:R1.2, MOT_MODULE_Y:R3.2, MOT_MODULE_Y:R5.2, MOT_MODULE_Y:SOCK.1, MOT_MODULE_Z:MD.5, MOT_MODULE_Z:MD.6, MOT_MODULE_Z:R1.2, MOT_MODULE_Z:R3.2, MOT_MODULE_Z:R5.2, MOT_MODULE_Z:SOCK.1, U1.19
EXT_24V: MOT_MODULE_X:MD.15, MOT_MODULE_Y:MD.15, MOT_MODULE_Z:MD.15
EXT_24V_GND: MOT_MODULE_X:MD.16, MOT_MODULE_Y:MD.16, MOT_MODULE_Z:MD.16
EXT_GND: C2.2, ETH0.J1.1, ETH0.J1.2, ETH0.J2.1, JP1.1, JP2.3, JP3.1, MOT_MODULE_X:MD.10, MOT_MODULE_X:R2.1, MOT_MODULE_X:R4.1, MOT_MODULE_X:R6.1, MOT_MODULE_X:SOCK.2, MOT_MODULE_Y:MD.10, MOT_MODULE_Y:R2.1, MOT_MODULE_Y:R4.1, MOT_MODULE_Y:R6.1, MOT_MODULE_Y:SOCK.2, MOT_MODULE_Z:MD.10, MOT_MODULE_Z:R2.1, MOT_MODULE_Z:R4.1, MOT_MODULE_Z:R6.1, MOT_MODULE_Z:SOCK.2, U1.38
MOTXY_M0: JP1.2, MOT_MODULE_X:MD.2, MOT_MODULE_Y:MD.2, MOT_MODULE_Z:MD.2
MOTXY_M1: JP2.2, MOT_MODULE_X:MD.3, MOT_MODULE_Y:MD.3, MOT_MODULE_Z:MD.3
MOTXY_M2: JP3.2, MOT_MODULE_X:MD.4, MOT_MODULE_Y:MD.4, MOT_MODULE_Z:MD.4
MOT_MODULE_X:!EN: MOT_MODULE_X:MD.1, MOT_MODULE_X:MDRIVER_X2.1
MOT_MODULE_X:MD_DIR: MOT_MODULE_X:MD.8, MOT_MODULE_X:MDRIVER_X2.3
MOT_MODULE_X:MD_STEP: MOT_MODULE_X:MD.7, MOT_MODULE_X:MDRIVER_X2.2
MOT_MODULE_X:MOT_A-: MOT_MODULE_X:MD.11, MOT_MODULE_X:MDRIVER_X2.7, MOT_MODULE_X:SOCK.7
MOT_MODULE_X:SENSOR_SFAR: MOT_MODULE_X:R5.1, MOT_MODULE_X:R6.2, MOT_MODULE_X:SOCK.5
MOT_MODULE_X:SENSOR_SMID: MOT_MODULE_X:R3.1, MOT_MODULE_X:R4.2, MOT_MODULE_X:SOCK.4
MOT_MODULE_X:SENSOR_SNEAR: MOT_MODULE_X:R1.1, MOT_MODULE_X:R2.2, MOT_MODULE_X:SOCK.3
MOT_MODULE_X:SOCK_A+: MOT_MODULE_X:MD.12, MOT_MODULE_X:MDRIVER_X2.6, MOT_MODULE_X:SOCK.6
MOT_MODULE_X:SOCK_B+: MOT_MODULE_X:MD.13, MOT_MODULE_X:MDRIVER_X2.8, MOT_MODULE_X:SOCK.8
MOT_MODULE_X:SOCK_B-: MOT_MODULE_X:MD.14, MOT_MODULE_X:MDRIVER_X2.9, MOT_MODULE_X:SOCK.9
MOT_MODULE_Y:!EN: MOT_MODULE_Y:MD.1, MOT_MODULE_Y:MDRIVER_X2.1
MOT_MODULE_Y:MD_DIR: MOT_MODULE_Y:MD.8, MOT_MODULE_Y:MDRIVER_X2.3
MOT_MODULE_Y:MD_STEP: MOT_MODULE_Y:MD.7, MOT_MODULE_Y:MDRIVER_X2.2
MOT_MODULE_Y:MOT_A-: MOT_MODULE_Y:MD.11, MOT_MODULE_Y:MDRIVER_X2.7, MOT_MODULE_Y:SOCK.7
MOT_MODULE_Y:SENSOR_SFAR: MOT_MODULE_Y:R5.1, MOT_MODULE_Y:R6.2, MOT_MODULE_Y:SOCK.5
MOT_MODULE_Y:SENSOR_SMID: MOT_MODULE_Y:R3.1, MOT_MODULE_Y:R4.2, MOT_MODULE_Y:SOCK.4
MOT_MODULE_Y:SENSOR_SNEAR: MOT_MODULE_Y:R1.1, MOT_MODULE_Y:R2.2, MOT_MODULE_Y:SOCK.3
MOT_MODULE_Y:SOCK_A+: MOT_MODULE_Y:MD.12, MOT_MODULE_Y:MDRIVER_X2.6, MOT_MODULE_Y:SOCK.6
MOT_MODULE_Y:SOCK_B+: MOT_MODULE_Y:MD.13, MOT_MODULE_Y:MDRIVER_X2.8, MOT_MODULE_Y:SOCK.8
MOT_MODULE_Y:SOCK_B-: MOT_MODULE_Y:MD.14, MOT_MODULE_Y:MDRIVER_X2.9, MOT_MODULE_Y:SOCK.9
MOT_MODULE_Z:!EN: MOT_MODULE_Z:MD.1, MOT_MODULE_Z:MDRIVER_X2.1
MOT_MODULE_Z:MD_DIR: MOT_MODULE_Z:MD.8, MOT_MODULE_Z:MDRIVER_X2.3
MOT_MODULE_Z:MD_STEP: MOT_MODULE_Z:MD.7, MOT_MODULE_Z:MDRIVER_X2.2
MOT_MODULE_Z:MOT_A-: MOT_MODULE_Z:MD.11, MOT_MODULE_Z:MDRIVER_X2.7, MOT_MODULE_Z:SOCK.7
MOT_MODULE_Z:SENSOR_SFAR: MOT_MODULE_Z:R5.1, MOT_MODULE_Z:R6.2, MOT_MODULE_Z:SOCK.5
MOT_MODULE_Z:SENSOR_SMID: MOT_MODULE_Z:R3.1, MOT_MODULE_Z:R4.2, MOT_MODULE_Z:SOCK.4
MOT_MODULE_Z:SENSOR_SNEAR: MOT_MODULE_Z:R1.1, MOT_MODULE_Z:R2.2, MOT_MODULE_Z:SOCK.3
MOT_MODULE_Z:SOCK_A+: MOT_MODULE_Z:MD.12, MOT_MODULE_Z:MDRIVER_X2.6, MOT_MODULE_Z:SOCK.6
MOT_MODULE_Z:SOCK_B+: MOT_MODULE_Z:MD.13, MOT_MODULE_Z:MDRIVER_X2.8, MOT_MODULE_Z:SOCK.8
MOT_MODULE_Z:SOCK_B-: MOT_MODULE_Z:MD.14, MOT_MODULE_Z:MDRIVER_X2.9, MOT_MODULE_Z:SOCK.9
U1_3V3: ETH0.J2.2, ETH0.J2.3, U1.1
U1_EN: C2.1, U1.2

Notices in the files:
parts and their libraries:
SparkFun-Connectors: Licensing: Creative Commons ShareAlike 4.0 International - https://creativecommons.org/licenses/by-sa/4.0
con-headers-jp: Copyright (C) 2008, Bob Starr
